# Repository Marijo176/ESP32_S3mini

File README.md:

# ESP32-S3-MINI Development Board

## Overview

Custom ESP32-S3-MINI development board designed in KiCad for wireless embedded systems and battery-powered applications.

## Hardware Features

* ESP32-S3-MINI module
* USB Type-C power and data interface
* 5 V DC barrel jack input
* BQ24040 single-cell Li-ion/LiPo battery charger
* TLV75801 adjustable voltage regulator configured for 3.3V
* ESD7104 USB ESD protection
* Schottky diode power input isolation
* 0.75 A hold-current resettable fuse
* JST battery connector
* UART and I2C communication interfaces
* BOOT and RESET push buttons
* Charging, power-good and power indicator LEDs

## PCB Specifications

| Parameter | Specification |
|---|---|
| PCB layers | 4 |
| PCB thickness | Approx. 1.6 mm |
| Input voltage | 5 V / single-cell Li-ion or LiPo battery |
| Operating voltage | 3.3 V |
| Design software | KiCad |

## PCB Layout

## Schematic

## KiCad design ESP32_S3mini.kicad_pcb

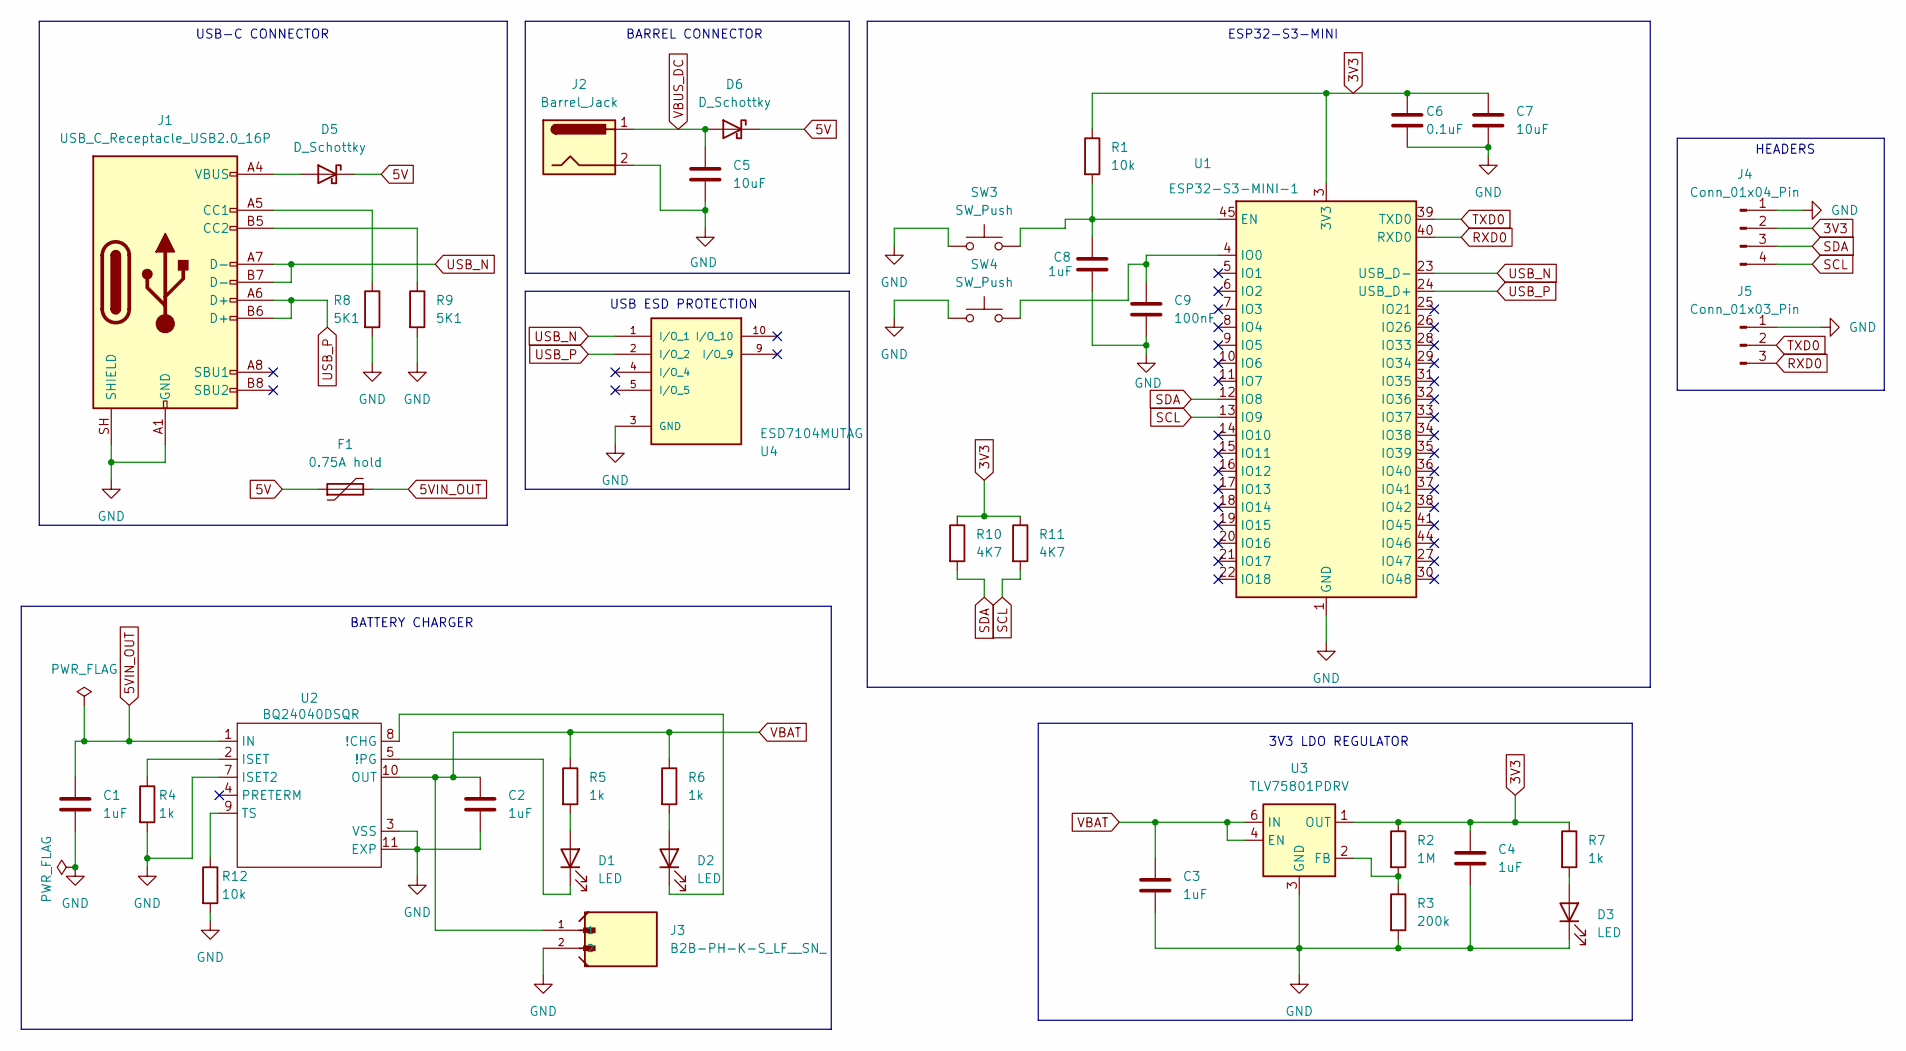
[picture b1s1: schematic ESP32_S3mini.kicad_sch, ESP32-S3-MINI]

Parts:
C1, C2, C3, C4, C8: 1uF; C_0603_1608Metric
C5, C7: 10uF; C_0603_1608Metric
C6: 0.1uF; C_0603_1608Metric
C9: 100nF; C_0603_1608Metric
D1, D2, D3: LED; LED_0603_1608Metric
D5, D6: D_Schottky; D_SMA
F1: 0.75A hold; Fuse_1206_3216Metric
J1: USB_C_Receptacle_USB2.0_16P; USB_C_Receptacle_GCT_USB4105-xx-A_16P_TopMnt_Horizontal
J2: Barrel_Jack; BarrelJack_CUI_PJ-102AH_Horizontal
J3: B2B-PH-K-S_LF__SN_; JST_B2B-PH-K-S_LF__SN_; MPN B2B-PH-K-S(LF)(SN)
J4: Conn_01x04_Pin; PinHeader_1x04_P2.54mm_Vertical
J5: Conn_01x03_Pin; PinHeader_1x03_P2.54mm_Vertical
R1, R12: 10k; R_0603_1608Metric
R2: 1M; R_0603_1608Metric
R3: 200k; R_0603_1608Metric
R4, R5, R6, R7: 1k; R_0603_1608Metric
R8, R9: 5K1; R_0603_1608Metric
R10, R11: 4K7; R_0603_1608Metric
SW3, SW4: SW_Push; SW_SPST_PTS810
U1: ESP32-S3-MINI-1; ESP32-S2-MINI-1
U2: BQ24040DSQR; Texas_DSQ0010A_WSON-10-1EP_2x2mm_P0.4mm_EP0.9x1.5mm
U3: TLV75801PDRV; WSON-6-1EP_2x2mm_P0.65mm_EP1x1.6mm
U4: ESD7104MUTAG; IC_ESD7104MUTAG; MPN ESD7104MUTAG

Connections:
3V3: C4.1, C6.1, C7.1, J4.2, R1.1, R2.1, R7.1, R10.1, R11.1, U1.3 (3V3), U3.1 (OUT)
5V: D5.1 (K), D6.1 (K), F1.1
5VIN_OUT: C1.1, F1.2, U2.1 (IN)
GND: C1.2, C2.2, C3.2, C4.2, C5.2, C6.2, C7.2, C8.2, C9.2, D3.1 (K), J1.A1 (GND), J1.A12 (GND), J1.B1 (GND), J1.B12 (GND), J1.SH (SHIELD), J2.2, J3.2, J4.1, J5.1, R3.2, R4.2, R8.2, R9.2, R12.2, SW3.1, SW4.1, U1.1 (GND), U1.2 (GND), U1.42 (GND), U1.43 (GND), U1.46 (GND), U1.47 (GND), U1.48 (GND), U1.49 (GND), U1.50 (GND), U1.51 (GND), U1.52 (GND), U1.53 (GND), U1.54 (GND), U1.55 (GND), U1.56 (GND), U1.57 (GND), U1.58 (GND), U1.59 (GND), U1.60 (GND), U1.61 (GND), U1.62 (GND), U1.63 (GND), U1.64 (GND), U1.65 (GND), U2.3 (VSS), U2.7 (ISET2), U2.11 (EXP), U3.3 (GND), U3.7 (GND), U4.3 (GND), U4.8 (GND)
unnamed: D1.2 (A), R5.2
unnamed: D1.1 (K), U2.5 (!PG)
unnamed: D2.2 (A), R6.2
unnamed: D2.1 (K), U2.8 (!CHG)
unnamed: D3.2 (A), R7.2
unnamed: D5.2 (A), J1.A4 (VBUS), J1.A9 (VBUS), J1.B4 (VBUS), J1.B9 (VBUS)
unnamed: J1.A5 (CC1), R8.1
unnamed: J1.B5 (CC2), R9.1
unnamed: C8.1, R1.2, SW3.2, U1.45 (EN)
unnamed: C9.1, SW4.2, U1.4 (IO0)
unnamed: R4.1, U2.2 (ISET)
unnamed: R12.1, U2.9 (TS)
unnamed: R2.2, R3.1, U3.2 (FB)
RXD0: J5.3, U1.40 (RXD0)
SCL: J4.4, R11.2, U1.13 (IO9)
SDA: J4.3, R10.2, U1.12 (IO8)
TXD0: J5.2, U1.39 (TXD0)
USB_N: J1.A7 (D-), J1.B7 (D-), U1.23 (USB_D-), U4.1 (I/O_1)
USB_P: J1.A6 (D+), J1.B6 (D+), U1.24 (USB_D+), U4.2 (I/O_2)
VBAT: C2.1, C3.1, J3.1, R5.1, R6.1, U2.10 (OUT), U3.4 (EN), U3.6 (IN)
VBUS_DC: C5.1, D6.2 (A), J2.1

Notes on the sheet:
3V3 LDO REGULATOR
USB ESD PROTECTION
HEADERS
ESP32-S3-MINI
USB-C CONNECTOR
BARREL CONNECTOR
BATTERY CHARGER

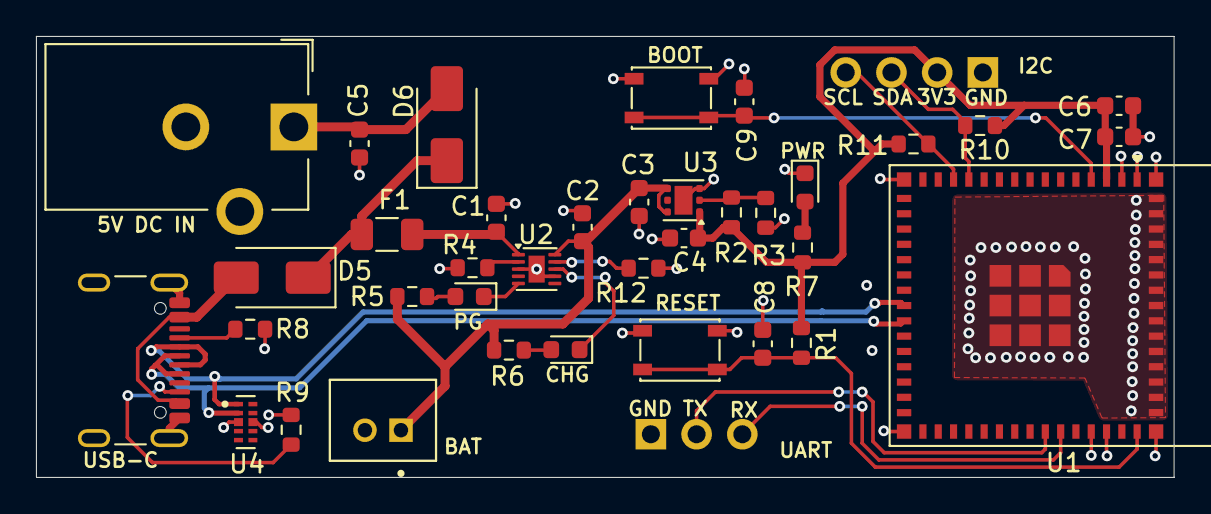
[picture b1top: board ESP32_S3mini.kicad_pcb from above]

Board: 4 copper layers, 63.2 x 24.5 mm, 38 parts (0 on the bottom side), 25 nets.
